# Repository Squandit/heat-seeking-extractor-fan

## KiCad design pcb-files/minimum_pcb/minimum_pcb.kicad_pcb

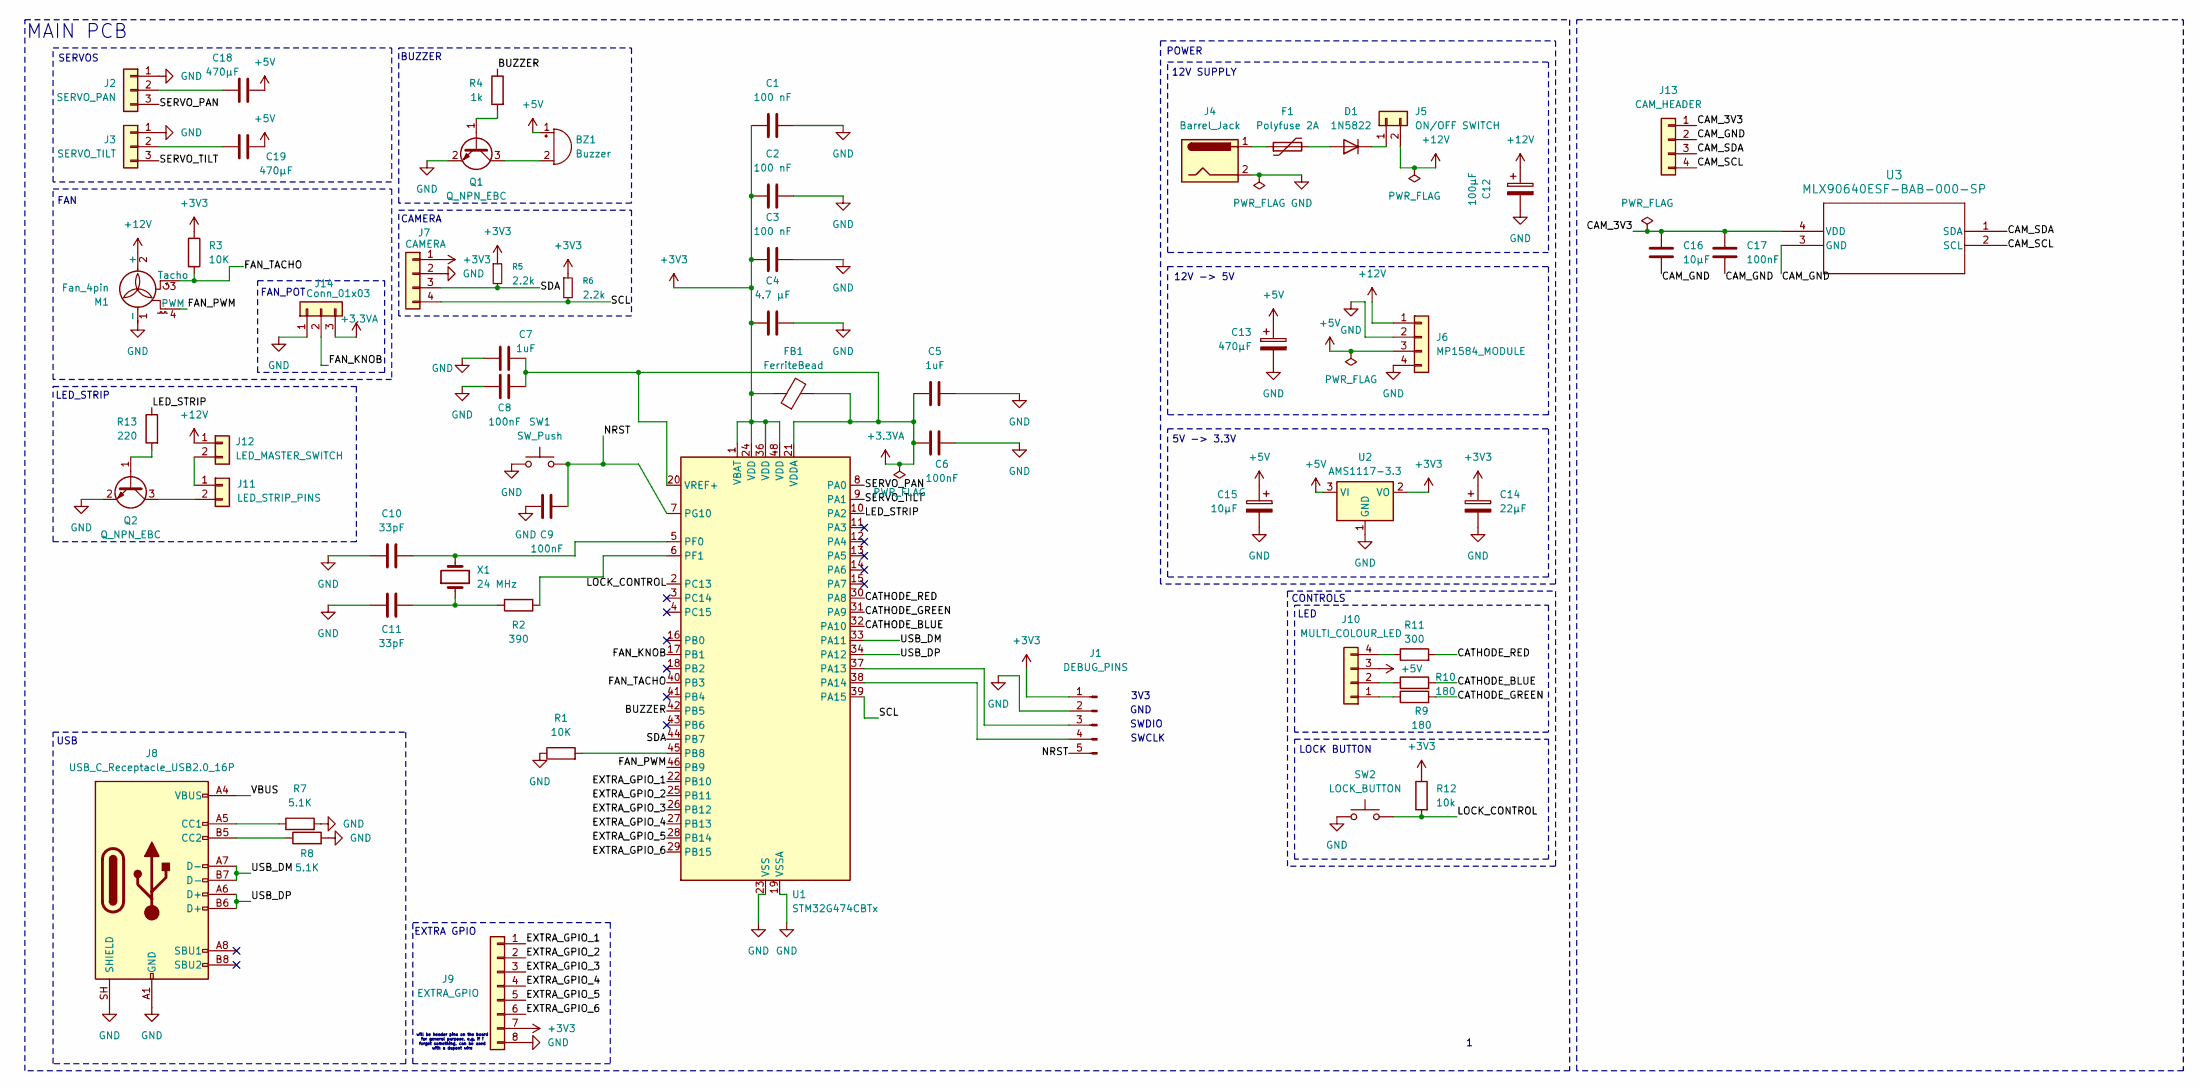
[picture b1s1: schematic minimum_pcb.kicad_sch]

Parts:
BZ1: Buzzer; Buzzer_TDK_PS1240P02BT_D12.2mm_H6.5mm
C1, C2, C3: 100 nF; C_Disc_D4.3mm_W1.9mm_P5.00mm
C4: 4.7 μF; C_Disc_D4.3mm_W1.9mm_P5.00mm
C5, C7: 1uF; C_Disc_D4.3mm_W1.9mm_P5.00mm
C6, C8, C9, C17: 100nF; C_Disc_D4.3mm_W1.9mm_P5.00mm
C10, C11: 33pF; C_Disc_D4.3mm_W1.9mm_P5.00mm
C12: 100µF; CP_Radial_D6.3mm_P2.50mm
C13, C18, C19: 470µF; CP_Radial_D8.0mm_P3.50mm
C14: 22µF; CP_Radial_D5.0mm_P2.00mm
C15, C16: 10µF; CP_Radial_D5.0mm_P2.00mm
D1: 1N5822; D_DO-201AD_P12.70mm_Horizontal
F1: Polyfuse 2A; Fuse_Bourns_MF-RG800
FB1: FerriteBead; WE-UKW_74275011
J1: DEBUG_PINS; PinHeader_1x05_P2.54mm_Vertical
J2: SERVO_PAN; PinHeader_1x03_P2.54mm_Vertical
J3: SERVO_TILT; PinHeader_1x03_P2.54mm_Vertical
J4: Barrel_Jack; BarrelJack_CUI_PJ-102AH_Horizontal
J5: ON/OFF SWITCH; PinHeader_1x02_P2.54mm_Vertical
J6: MP1584_MODULE; PinHeader_1x04_P2.54mm_Vertical
J7: CAMERA; PinHeader_1x04_P2.54mm_Vertical
J8: USB_C_Receptacle_USB2.0_16P; USB_C_Receptacle_GCT_USB4105-xx-A_16P_TopMnt_Horizontal
J9: EXTRA_GPIO; PinHeader_2x04_P2.54mm_Vertical
J10: MULTI_COLOUR_LED; PinHeader_1x04_P2.54mm_Vertical
J11: LED_STRIP_PINS; PinHeader_1x02_P2.54mm_Vertical
J12: LED_MASTER_SWITCH; PinHeader_1x02_P2.54mm_Vertical
J13: CAM_HEADER; PinHeader_1x04_P2.54mm_Vertical
J14: Conn_01x03; PinHeader_1x03_P2.54mm_Vertical
M1: Fan_4pin; PinHeader_1x04_P2.54mm_Vertical
Q1, Q2: Q_NPN_EBC; TO-92_Inline_Wide
R1, R3: 10K; R_Axial_DIN0207_L6.3mm_D2.5mm_P7.62mm_Horizontal
R2: 390; R_Axial_DIN0207_L6.3mm_D2.5mm_P7.62mm_Horizontal
R4: 1k; R_Axial_DIN0207_L6.3mm_D2.5mm_P7.62mm_Horizontal
R5, R6: 2.2k; R_Axial_DIN0207_L6.3mm_D2.5mm_P7.62mm_Horizontal
R7, R8: 5.1K; R_Axial_DIN0207_L6.3mm_D2.5mm_P7.62mm_Horizontal
R9, R10: 180; R_Axial_DIN0207_L6.3mm_D2.5mm_P7.62mm_Horizontal
R11: 300; R_Axial_DIN0207_L6.3mm_D2.5mm_P7.62mm_Horizontal
R12: 10k; R_Axial_DIN0207_L6.3mm_D2.5mm_P7.62mm_Horizontal
R13: 220; R_Axial_DIN0207_L6.3mm_D2.5mm_P7.62mm_Horizontal
SW1: SW_Push; PinHeader_1x02_P2.54mm_Vertical
SW2: LOCK_BUTTON; PinHeader_1x02_P2.54mm_Vertical
U1: STM32G474CBTx; LQFP-48_7x7mm_P0.5mm
U2: AMS1117-3.3; SOT-223-3_TabPin2
U3: MLX90640ESF-BAB-000-SP; MLX90640_MEL
X1: 24 MHz; Crystal_HC49-4H_Vertical

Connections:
+3.3VA: C5.1, C6.1, C7.2, C8.2, FB1.2, J14.3, U1.20 (VREF+), U1.21 (VDDA)
+3V3: C1.1, C2.1, C3.1, C4.1, C14.1, FB1.1, J1.1, J7.1, J9.7, R3.1, R5.1, R6.1, R12.1, U1.1 (VBAT), U1.24 (VDD), U1.36 (VDD), U1.48 (VDD), U2.2 (VO)
+5V: BZ1.1 (+), C13.1, C15.1, C18.2, C19.2, J6.3, J10.3, U2.3 (VI)
+12V: C12.1, J5.2, J6.1, J12.1, M1.2 (+)
/BUZZER: R4.1, U1.42 (PB5)
/CAM_3V3: C16.1, C17.1, J13.1, U3.4 (VDD)
/CAM_GND: C16.2, C17.2, J13.2, U3.3 (GND)
/CAM_SCL: J13.4, U3.2 (SCL)
/CAM_SDA: J13.3, U3.1 (SDA)
/CATHODE_BLUE: R10.2, U1.32 (PA10)
/CATHODE_GREEN: R9.2, U1.31 (PA9)
/CATHODE_RED: R11.2, U1.30 (PA8)
/EXTRA_GPIO_1: J9.1, U1.22 (PB10)
/EXTRA_GPIO_2: J9.2, U1.25 (PB11)
/EXTRA_GPIO_3: J9.3, U1.26 (PB12)
/EXTRA_GPIO_4: J9.4, U1.27 (PB13)
/EXTRA_GPIO_5: J9.5, U1.28 (PB14)
/EXTRA_GPIO_6: J9.6, U1.29 (PB15)
/FAN_KNOB: J14.2, U1.17 (PB1)
/FAN_PWM: M1.4 (PWM), U1.46 (PB9)
/FAN_TACHO: M1.3 (Tacho), R3.2, U1.40 (PB3)
/LED_STRIP: R13.1, U1.10 (PA2)
/LOCK_CONTROL: R12.2, SW2.1, U1.2 (PC13)
/NRST: C9.2, J1.5, SW1.2, U1.7 (PG10)
/SCL: J7.4, R6.2, U1.39 (PA15)
/SDA: J7.3, R5.2, U1.44 (PB7)
/SERVO_PAN: J2.3, U1.8 (PA0)
/SERVO_TILT: J3.3, U1.9 (PA1)
/USB_DM: J8.A7 (D-), J8.B7 (D-), U1.33 (PA11)
/USB_DP: J8.A6 (D+), J8.B6 (D+), U1.34 (PA12)
/VBUS: J8.A4 (VBUS), J8.A9 (VBUS), J8.B4 (VBUS), J8.B9 (VBUS)
GND: C1.2, C2.2, C3.2, C4.2, C5.2, C6.2, C7.1, C8.1, C9.1, C10.1, C11.2, C12.2, C13.2, C14.2, C15.2, J1.2, J2.1, J3.1, J4.2, J6.2, J6.4, J7.2, J8.A1 (GND), J8.A12 (GND), J8.B1 (GND), J8.B12 (GND), J8.SH (SHIELD), J9.8, J14.1, M1.1 (-), Q1.2 (E), Q2.2 (E), R1.1, R7.2, R8.2, SW1.1, SW2.2, U1.19 (VSSA), U1.23 (VSS), U1.35 (VSS), U1.47 (VSS), U2.1 (GND)
unnamed: BZ1.2 (-), Q1.3 (C)
unnamed: C11.1, R2.2, X1.1
unnamed: D1.2 (A), F1.2
unnamed: D1.1 (K), J5.1
unnamed: F1.1, J4.1
unnamed: J1.3, U1.37 (PA13)
unnamed: J1.4, U1.38 (PA14)
unnamed: C18.1, J2.2
unnamed: C19.1, J3.2
unnamed: J8.A5 (CC1), R7.1
unnamed: J8.B5 (CC2), R8.1
unnamed: J10.1, R9.1
unnamed: J10.2, R10.1
unnamed: J10.4, R11.1
unnamed: J11.1, J12.2
unnamed: J11.2, Q2.3 (C)
unnamed: Q1.1 (B), R4.2
unnamed: Q2.1 (B), R13.2
unnamed: R1.2, U1.45 (PB8)
unnamed: C10.2, U1.5 (PF0), X1.2
unnamed: R2.1, U1.6 (PF1)

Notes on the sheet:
BUZZER
FAN_POT
LED
GND
USB
12V SUPPLY
12V -> 5V
LOCK BUTTON
will be header pins on the board for general purpose, e.g. if i forget something, can be used with a dupont wire
MAIN PCB
CAMERA
SWDIO
3V3
CONTROLS
5V -> 3.3V
FAN
EXTRA GPIO
LED_STRIP
POWER
SERVOS
SWCLK

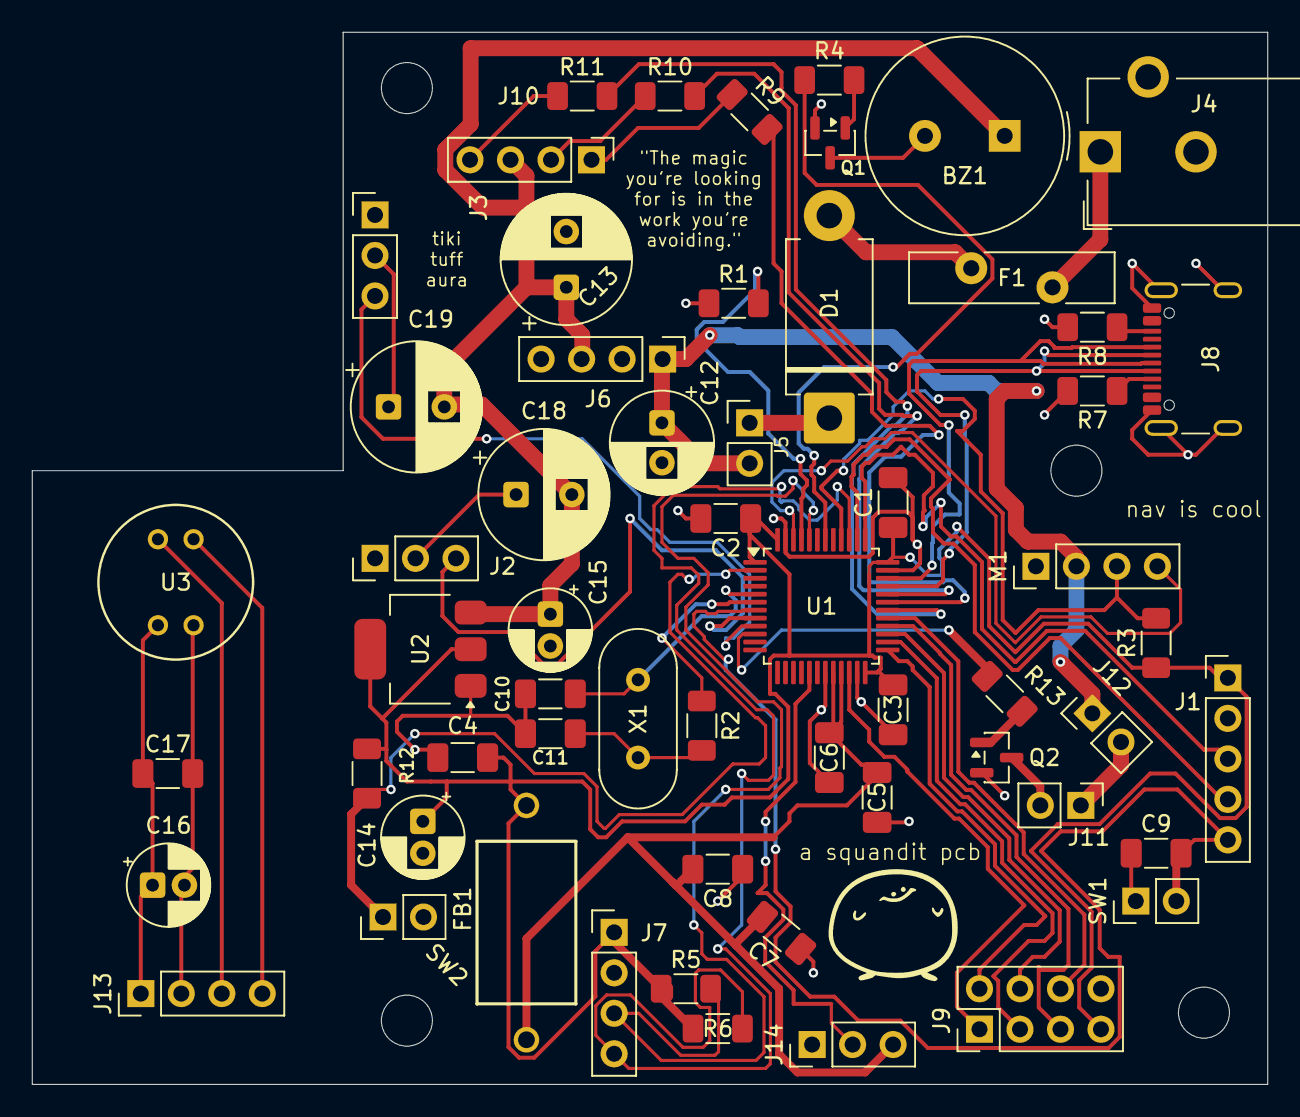
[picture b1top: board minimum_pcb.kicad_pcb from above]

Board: 2 copper layers, 77.5 x 66.0 mm, 59 parts (0 on the bottom side), 53 nets.

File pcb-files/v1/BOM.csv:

"Reference","Qty","Value","Exclude from Simulation","Exclude from Position Files"
"BZ1","1","Buzzer","","${EXCLUDE_FROM_POS_FILES}"
"C1,C2,C3","3","100 nF","","${EXCLUDE_FROM_POS_FILES}"
"C4","1","4.7 μF","","${EXCLUDE_FROM_POS_FILES}"
"C5,C7","2","1uF","","${EXCLUDE_FROM_POS_FILES}"
"C6,C8,C9","3","100nF","","${EXCLUDE_FROM_POS_FILES}"
"C10,C11","2","20pF","","${EXCLUDE_FROM_POS_FILES}"
"C12","1","100µF","","${EXCLUDE_FROM_POS_FILES}"
"C13","1","470µF","","${EXCLUDE_FROM_POS_FILES}"
"C14","1","22µF","","${EXCLUDE_FROM_POS_FILES}"
"C15","1","10µF","","${EXCLUDE_FROM_POS_FILES}"
"D1","1","SS34","","${EXCLUDE_FROM_POS_FILES}"
"F1","1","Polyfuse 2A","","${EXCLUDE_FROM_POS_FILES}"
"FB1","1","FerriteBead","","${EXCLUDE_FROM_POS_FILES}"
"J1","1","Conn_01x05_Pin","","${EXCLUDE_FROM_POS_FILES}"
"J2","1","SERVO_PAN","","${EXCLUDE_FROM_POS_FILES}"
"J3","1","SERVO_TILT","","${EXCLUDE_FROM_POS_FILES}"
"J4","1","Barrel_Jack","","${EXCLUDE_FROM_POS_FILES}"
"J5","1","ON/OFF SWITCH","","${EXCLUDE_FROM_POS_FILES}"
"J6","1","MP1584_MODULE","","${EXCLUDE_FROM_POS_FILES}"
"J7","1","CAMERA","","${EXCLUDE_FROM_POS_FILES}"
"J8","1","USB_C_Receptacle_USB2.0_16P","","${EXCLUDE_FROM_POS_FILES}"
"J9","1","EXTRA_GPIO","","${EXCLUDE_FROM_POS_FILES}"
"M1","1","Fan_4pin","","${EXCLUDE_FROM_POS_FILES}"
"Q1","1","Q_NPN_BEC","","${EXCLUDE_FROM_POS_FILES}"
"R1,R3,RV1","3","10K","","${EXCLUDE_FROM_POS_FILES}"
"R2","1","390","","${EXCLUDE_FROM_POS_FILES}"
"R4","1","1k","","${EXCLUDE_FROM_POS_FILES}"
"R5,R6","2","2.2k","","${EXCLUDE_FROM_POS_FILES}"
"R7,R8","2","5.1K","","${EXCLUDE_FROM_POS_FILES}"
"SW1","1","SW_Push","","${EXCLUDE_FROM_POS_FILES}"
"U1","1","STM32G474CBTx","","${EXCLUDE_FROM_POS_FILES}"
"U2","1","AMS1117-3.3","","${EXCLUDE_FROM_POS_FILES}"
"X1","1","24 MHz","","${EXCLUDE_FROM_POS_FILES}"

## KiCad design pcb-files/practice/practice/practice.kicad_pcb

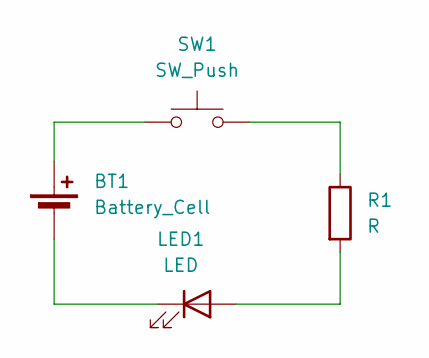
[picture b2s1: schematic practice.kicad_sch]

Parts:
BT1: Battery_Cell; BatteryHolder_Keystone_1060_1x2032
LED1: LED; LED_D5.0mm
R1: R; R_Axial_DIN0207_L6.3mm_D2.5mm_P10.16mm_Horizontal
SW1: SW_Push; SW_PUSH_6mm

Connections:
unnamed: BT1.1 (+), SW1.1
unnamed: BT1.2 (-), LED1.1 (K)
unnamed: LED1.2 (A), R1.2
unnamed: R1.1, SW1.2

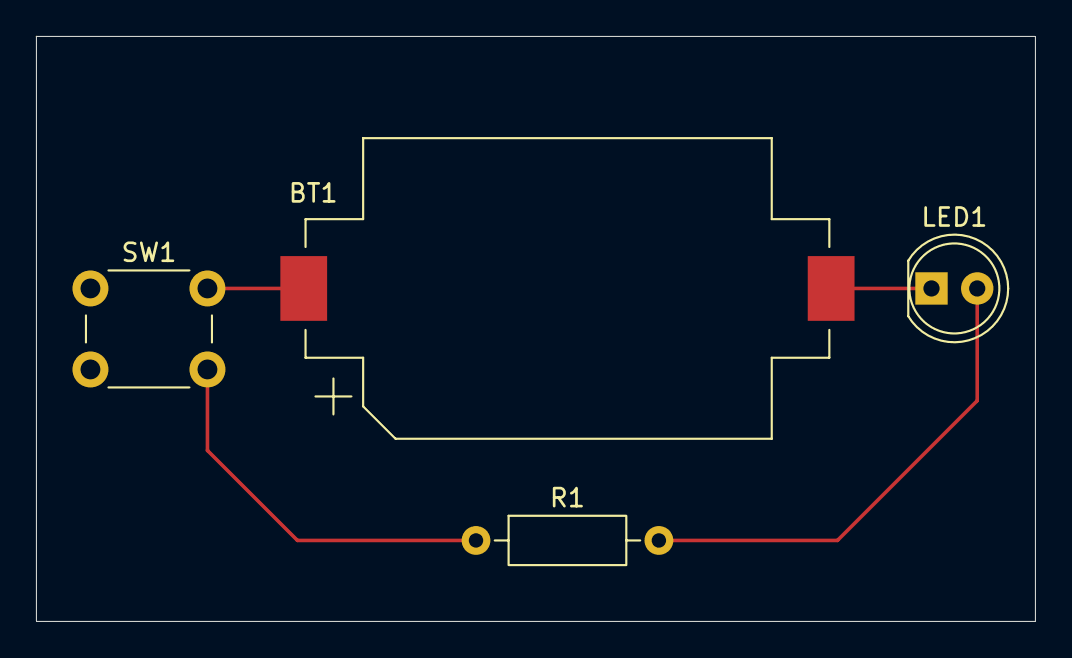
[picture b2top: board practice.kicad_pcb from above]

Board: 2 copper layers, 55.5 x 32.5 mm, 4 parts (0 on the bottom side), 4 nets.
